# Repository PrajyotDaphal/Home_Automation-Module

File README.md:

# 🏠 Home Automation Control Module (PCB Based)

## 📌 Project Overview

This project is a **PCB-based Home Automation Control Module** designed to control multiple AC appliances safely using relay isolation. The system uses optocouplers for electrical isolation, transistor drivers for relay switching, and an onboard AC-to-DC power module to power the control circuit.

The module can be controlled using:

* Microcontroller (ESP8266, Arduino, etc.)
* External digital logic
* Smartphone-based IoT system
* Manual control system

This design ensures **safety, reliability, and industrial-level performance**.

---

## ✨ Features

* Control up to **8 AC appliances**
* **Complete electrical isolation** using PC817 optocouplers
* **Onboard AC-DC converter (HLK-10M05)** – no external power supply required
* **Relay driver circuit using BC547 transistors**
* **Flyback diode protection** for relays
* **Status LEDs for each channel**
* **RC snubber for noise protection**
* **Compact and optimized PCB layout**
* Suitable for:

  * Home automation
  * Industrial automation
  * IoT systems
  * Smart switchboards

---

## 🔧 Hardware Components

| Component                             | Quantity |
| ------------------------------------- | -------- |
| HLK-10M05 AC-DC Module                | 1        |
| Relay (5V)                            | 8        |
| PC817 Optocoupler                     | 8        |
| BC547 Transistor                      | 8        |
| 1N4007 Diode                          | 8+       |
| LEDs                                  | 8        |
| Resistors (330Ω, 1kΩ, 220kΩ, etc.)    | Multiple |
| Capacitors (Electrolytic and Ceramic) | Multiple |
| Screw Terminals                       | Multiple |
| Buzzer                                | 1        |
| MOV (optional safety)                 | 1        |

---

## ⚡ Power Supply

**Input:**

* 230V AC mains

**Output:**

* 5V DC (from HLK-10M05)

Used to power:

* Optocouplers
* Relay coils
* Logic circuit

---

## 🔌 Pin Configuration

### Input Control Header

| Pin | Function        |
| --- | --------------- |
| IN1 | Relay 1 control |
| IN2 | Relay 2 control |
| IN3 | Relay 3 control |
| IN4 | Relay 4 control |
| IN5 | Relay 5 control |
| IN6 | Relay 6 control |
| IN7 | Relay 7 control |
| IN8 | Relay 8 control |
| VCC | 5V              |
| GND | Ground          |

---

## 🔄 Working Principle

1. Control signal applied to input pin
2. Optocoupler provides isolation
3. Transistor amplifies signal
4. Relay activates
5. Appliance turns ON/OFF

Isolation ensures protection from high voltage.

---

## 📷 Schematic

---

## 🧩| Full Layout | Upper Copper |

---

## 🔷 PCB 3D View

---

## 🛡️ Safety Features

* Optocoupler isolation
* Flyback diode protection
* RC snubber protection
* Proper PCB trace width for AC
* Separate AC and DC sections
* Fuse protection support

---

## 🌐 Applications

* Smart Home Automation
* IoT Control Systems
* Industrial Automation
* Remote Appliance Control
* Smart Switchboard

---

## 🧠 Compatible Controllers

* ESP8266
* ESP32
* Arduino Uno / Nano
* Raspberry Pi
* Any microcontroller with GPIO output

---

## 📁 Project Structure

```
Home-Automation-PCB/
│
├── KiCAD/
│   └── home_automation.kicad_pcb
│   └── home_automation.kicad_sch
│   └── home_automation.kicad_prl
│   └── home_automation.kicad_pro
│   └── home_automation.dsn
│ 
├── images/
│   ├── schematic.png
│   └── pcb_layout.png
|   └── 3D_View.png
|   └── Upper_Copper.png
│
├── gerber/
│   └── production files
|
├── gerber/Drill
│   └── production files
│
└── README.md
```

---

## 🚀 How to Use

1. Connect AC mains input
2. Connect appliances to relay terminals
3. Connect microcontroller to input header
4. Apply control signal
5. Appliance will turn ON/OFF

---

## ⚠️ Warning

This project uses **HIGH VOLTAGE AC**.

* Do not touch while powered
* Use proper insulation
* Use fuse and enclosure
* Only trained persons should handle

---

## 📌 Author

**Project by:** Prajyot Daphal
**Designed using:** KiCad
**Type:** Home Automation PCB Module

---

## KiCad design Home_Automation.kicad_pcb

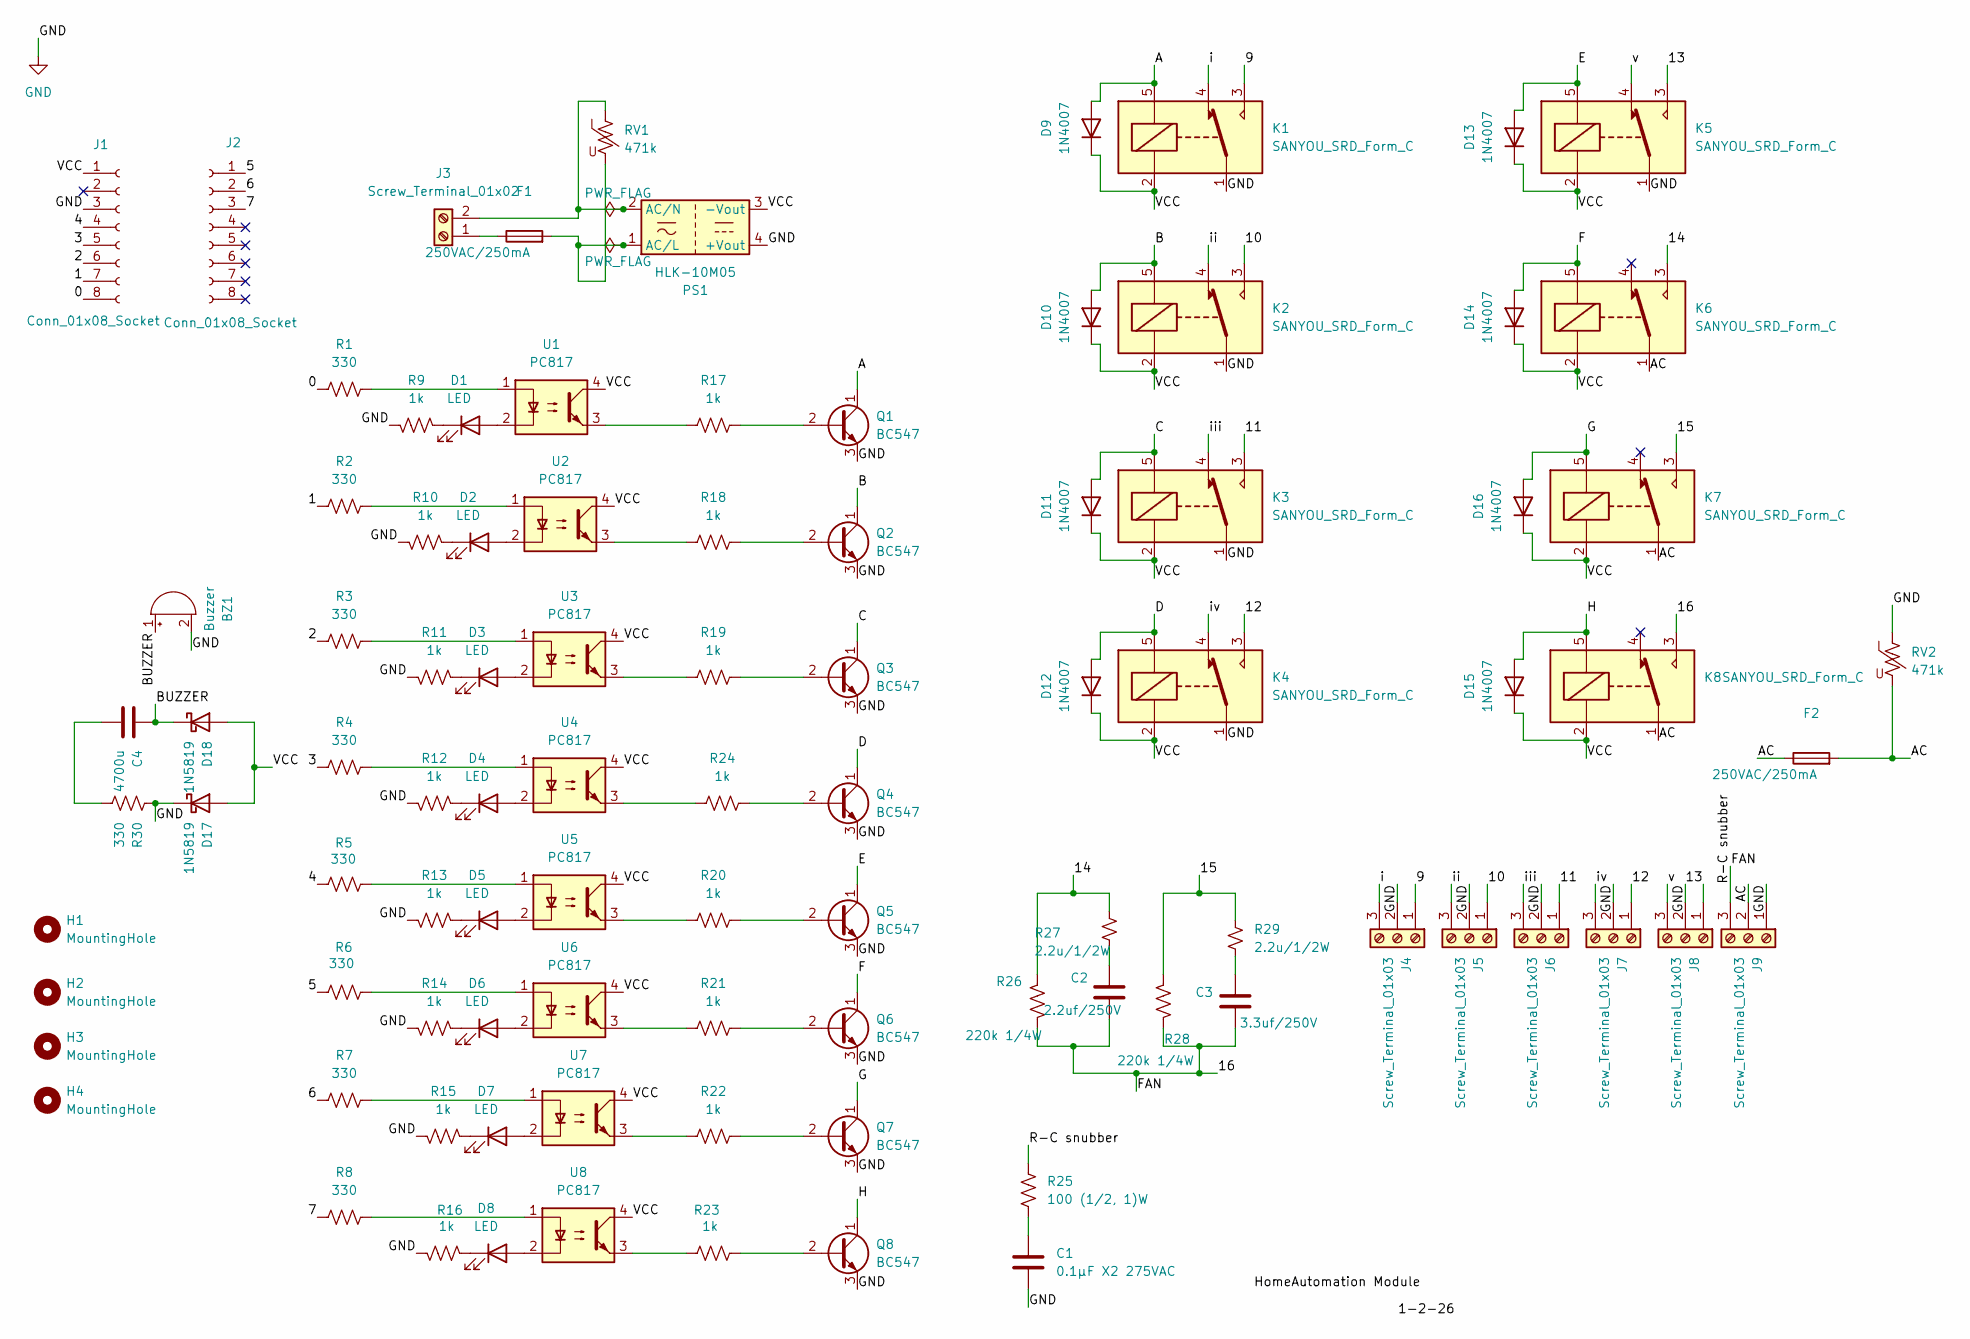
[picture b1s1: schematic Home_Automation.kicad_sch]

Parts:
BZ1: Buzzer; MagneticBuzzer_ProSignal_ABT-410-RC
C1: 0.1µF X2 275VAC; C_Rect_L18.0mm_W5.0mm_P15.00mm_FKS3_FKP3
C2: 2.2uf/250V; C_Rect_L31.5mm_W11.0mm_P27.50mm_MKS4
C3: 3.3uf/250V; C_Rect_L31.5mm_W11.0mm_P27.50mm_MKS4
C4: 4700u; C_Radial_D16.0mm_H25.0mm_P7.50mm
D1, D2, D3, D4, D5, D6, D7, D8: LED; LED_D3.0mm
D9, D10, D11, D12, D13, D14, D15, D16: 1N4007; D_DO-41_SOD81_P10.16mm_Horizontal
D17, D18: 1N5819; D_DO-41_SOD81_P10.16mm_Horizontal
F1, F2: 250VAC/250mA; Fuseholder_Cylinder-5x20mm_Schurter_0031_8201_Horizontal_Op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
H1, H2, H3, H4: MountingHole; MountingHole_5.3mm_M5
J1, J2: Conn_01x08_Socket; PinSocket_1x08_P2.54mm_Vertical
J3: Screw_Terminal_01x02; TerminalBlock_Phoenix_MKDS-1,5-2-5.08_1x02_P5.08mm_Horizont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
J4, J5, J6, J7, J8, J9: Screw_Terminal_01x03; TerminalBlock_Phoenix_MKDS-1,5-3_1x03_P5.00mm_Horizontal
K1, K2, K3, K4, K5, K6, K7, K8: SANYOU_SRD_Form_C; Relay_SPDT_SANYOU_SRD_Series_Form_C
PS1: HLK-10M05; Converter_ACDC_Hi-Link_HLK-10Mxx
Q1, Q2, Q3, Q4, Q5, Q6, Q7, Q8: BC547; TO-92_Inline
R1, R2, R3, R4, R5, R6, R7, R8, R30: 330; R_Axial_DIN0309_L9.0mm_D3.2mm_P15.24mm_Horizontal
R9, R10, R11, R12, R13, R14, R15, R16, R17, R18, R19, R20, R21, R22, R23, R24: 1k; R_Axial_DIN0309_L9.0mm_D3.2mm_P15.24mm_Horizontal
R25: 100 (1/2, 1)W; R_Axial_DIN0309_L9.0mm_D3.2mm_P15.24mm_Horizontal
R26, R28: 220k 1/4W; R_Axial_DIN0309_L9.0mm_D3.2mm_P15.24mm_Horizontal
R27, R29: 2.2u/1/2W; R_Axial_DIN0309_L9.0mm_D3.2mm_P15.24mm_Horizontal
RV1, RV2: 471k; RV_Disc_D16.5mm_W6.7mm_P7.5mm
U1, U2, U3, U4, U5, U6, U7, U8: PC817; DIP-4_W7.62mm

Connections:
/0: J1.8, R1.2
/1: J1.7, R2.2
/2: J1.6, R3.2
/3: J1.5, R4.2
/4: J1.4, R5.2
/5: J2.1, R6.2
/6: J2.2, R7.2
/7: J2.3, R8.2
/9: J4.1, K1.3
/10: J5.1, K2.3
/11: J6.1, K3.3
/12: J7.1, K4.3
/13: J8.1, K5.3
/14: K6.3, R26.1, R27.1
/15: K7.3, R28.1, R29.1
/16: C2.2, C3.2, J9.3, K8.3, R25.1, R26.2, R28.2
/A: D9.2 (A), K1.5, Q1.1 (C)
/B: D10.2 (A), K2.5, Q2.1 (C)
/BUZZER: BZ1.1 (+), C4.1, D18.1 (K)
/C: D11.2 (A), K3.5, Q3.1 (C)
/D: D12.2 (A), K4.5, Q4.1 (C)
/E: D13.2 (A), K5.5, Q5.1 (C)
/F: D14.2 (A), K6.5, Q6.1 (C)
/G: D16.2 (A), K7.5, Q7.1 (C)
/H: D15.2 (A), K8.5, Q8.1 (C)
/VCC: D9.1 (K), D10.1 (K), D11.1 (K), D12.1 (K), D13.1 (K), D14.1 (K), D15.1 (K), D16.1 (K), D17.2 (A), D18.2 (A), J1.1, K1.2, K2.2, K3.2, K4.2, K5.2, K6.2, K7.2, K8.2, PS1.3 (-Vout), U1.4, U2.4, U3.4, U4.4, U5.4, U6.4, U7.4, U8.4
/i: J4.3, K1.4
/ii: J5.3, K2.4
/iii: J6.3, K3.4
/iv: J7.3, K4.4
/v: J8.3, K5.4
unnamed: C1.1, R25.2
unnamed: C2.1, R27.2
unnamed: C3.1, R29.2
unnamed: C4.2, R30.2
unnamed: D1.2 (A), U1.2
unnamed: D1.1 (K), R9.2
unnamed: D2.2 (A), U2.2
unnamed: D2.1 (K), R10.2
unnamed: D3.2 (A), U3.2
unnamed: D3.1 (K), R11.2
unnamed: D4.2 (A), U4.2
unnamed: D4.1 (K), R12.2
unnamed: D5.2 (A), U5.2
unnamed: D5.1 (K), R13.2
unnamed: D6.2 (A), U6.2
unnamed: D6.1 (K), R14.2
unnamed: D7.2 (A), U7.2
unnamed: D7.1 (K), R15.2
unnamed: D8.2 (A), U8.2
unnamed: D8.1 (K), R16.2
unnamed: F1.1, J3.1
unnamed: J3.2, PS1.2 (AC/N), RV1.1
unnamed: F1.2, PS1.1 (AC/L), RV1.2
unnamed: Q1.2 (B), R17.1
unnamed: Q2.2 (B), R18.1
unnamed: Q3.2 (B), R19.1
unnamed: Q4.2 (B), R24.1
unnamed: Q5.2 (B), R20.1
unnamed: Q6.2 (B), R21.1
unnamed: Q7.2 (B), R22.1
unnamed: Q8.2 (B), R23.1
unnamed: R1.1, U1.1
unnamed: R2.1, U2.1
unnamed: R3.1, U3.1
unnamed: R4.1, U4.1
unnamed: R5.1, U5.1
unnamed: R6.1, U6.1
unnamed: R7.1, U7.1
unnamed: R8.1, U8.1
unnamed: R17.2, U1.3
unnamed: R18.2, U2.3
unnamed: R19.2, U3.3
unnamed: R20.2, U5.3
unnamed: R21.2, U6.3
unnamed: R22.2, U7.3
unnamed: R23.2, U8.3
unnamed: R24.2, U4.3

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
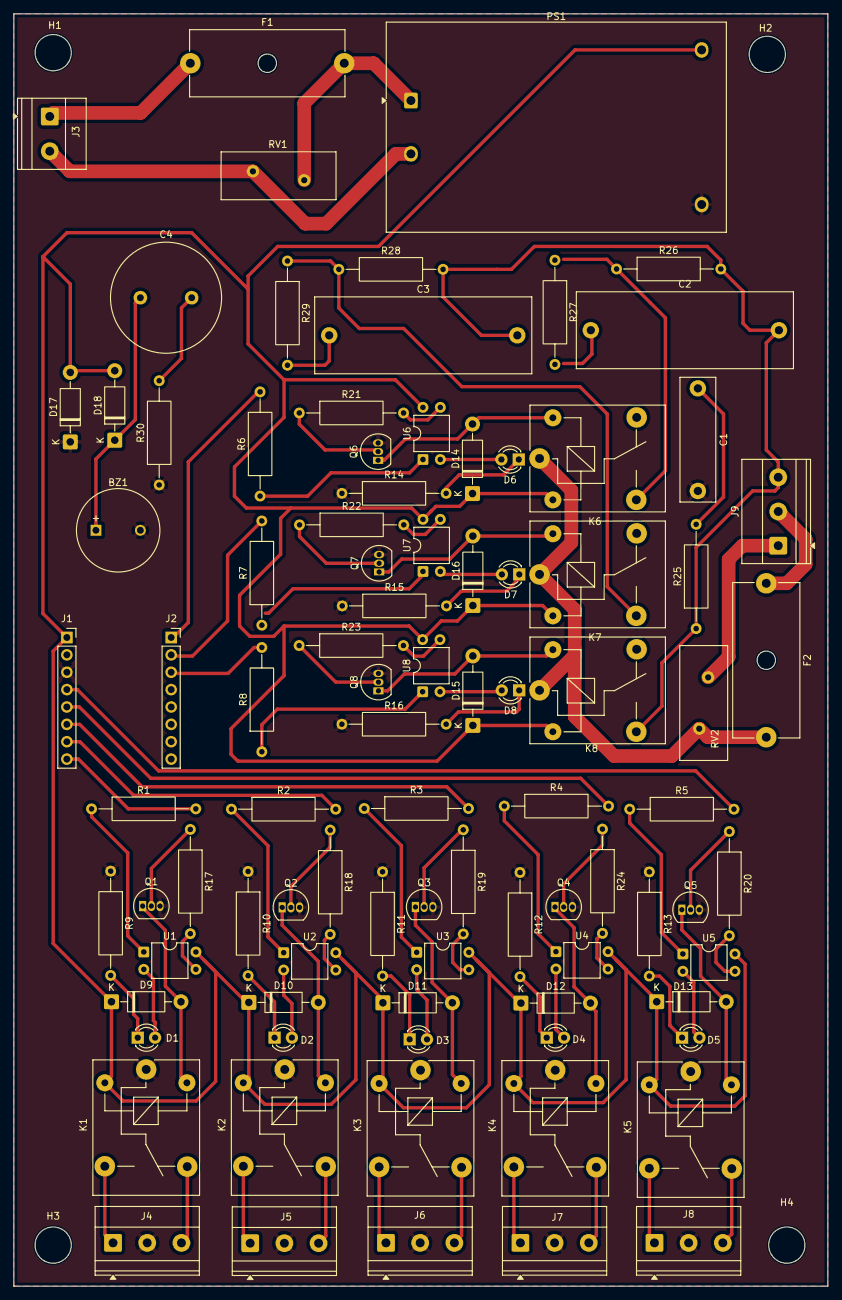
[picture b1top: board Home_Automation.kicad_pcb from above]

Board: 2 copper layers, 119.0 x 186.0 mm, 95 parts (0 on the bottom side), 82 nets.

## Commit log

2026-02-23 Create Drill
2026-02-23 Revise README for Home Automation Control Module
    Expanded project overview, features, hardware components, and usage instructions for the Home Automation Control Module.
2026-02-23 Update project author name in README
2026-02-23 Create SECURITY.md for security policy
    Added a security policy document outlining supported versions and vulnerability reporting.
